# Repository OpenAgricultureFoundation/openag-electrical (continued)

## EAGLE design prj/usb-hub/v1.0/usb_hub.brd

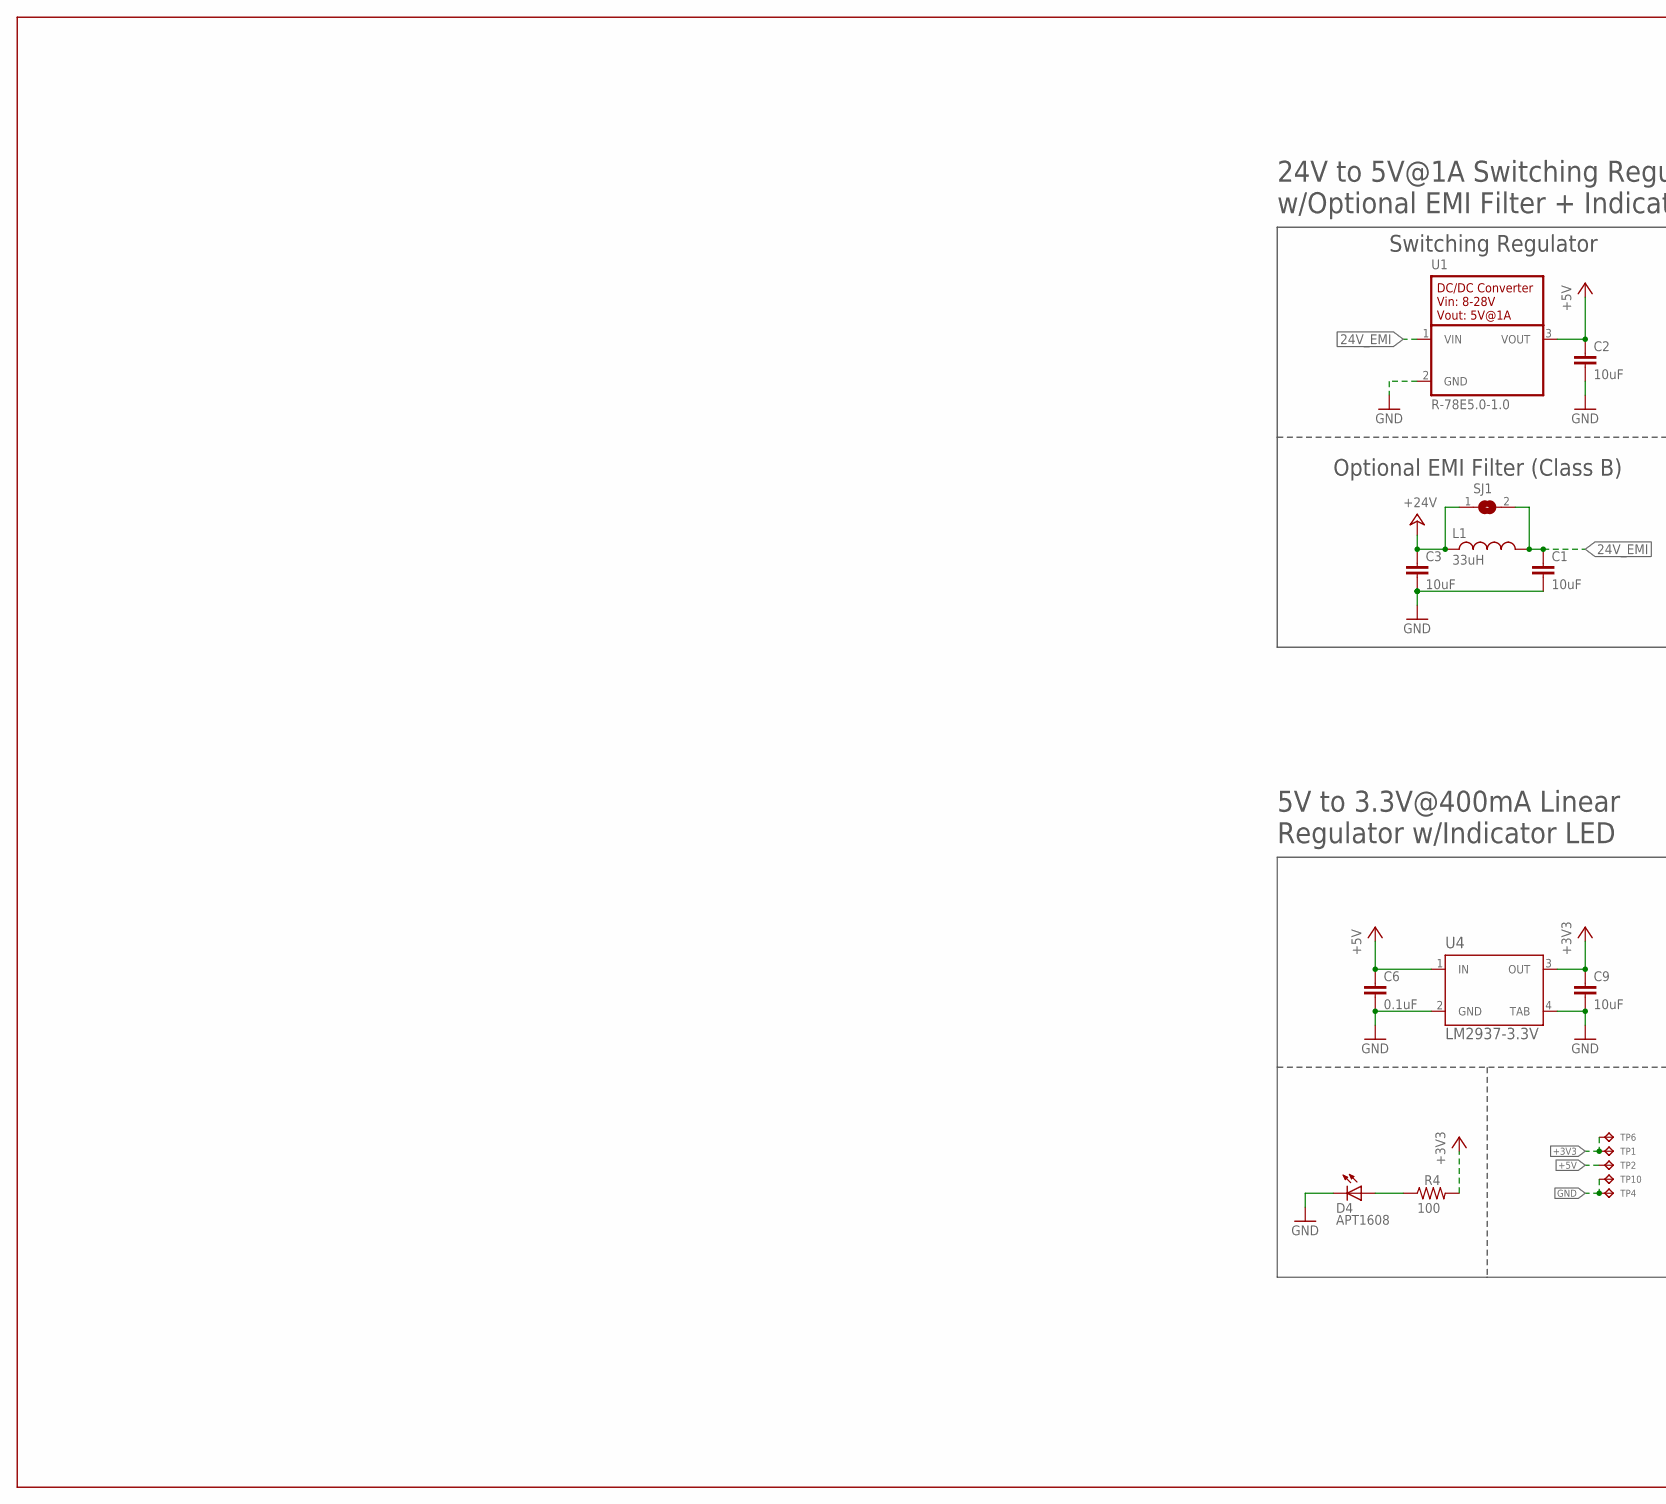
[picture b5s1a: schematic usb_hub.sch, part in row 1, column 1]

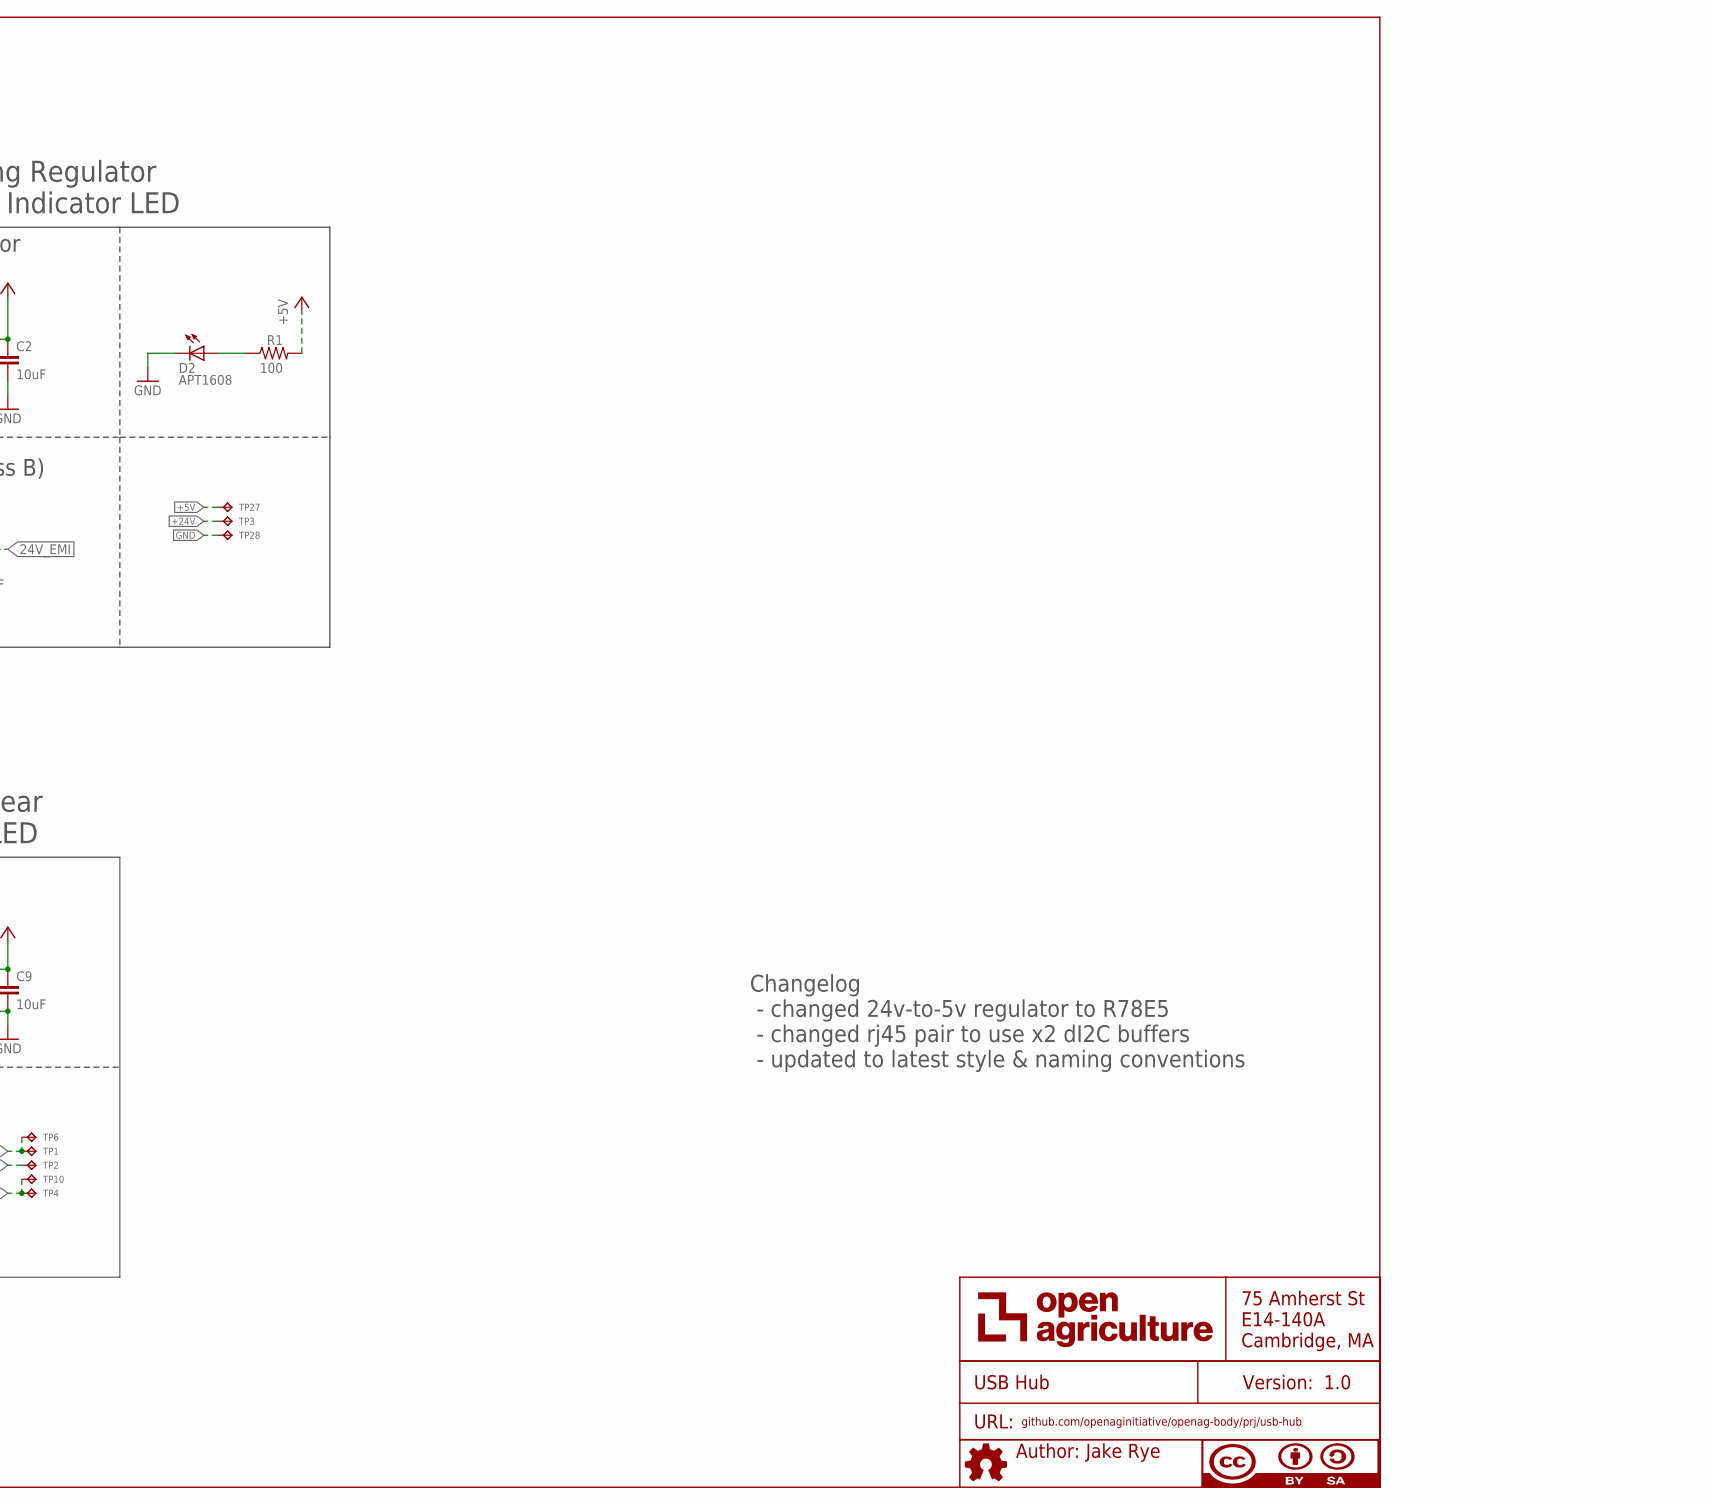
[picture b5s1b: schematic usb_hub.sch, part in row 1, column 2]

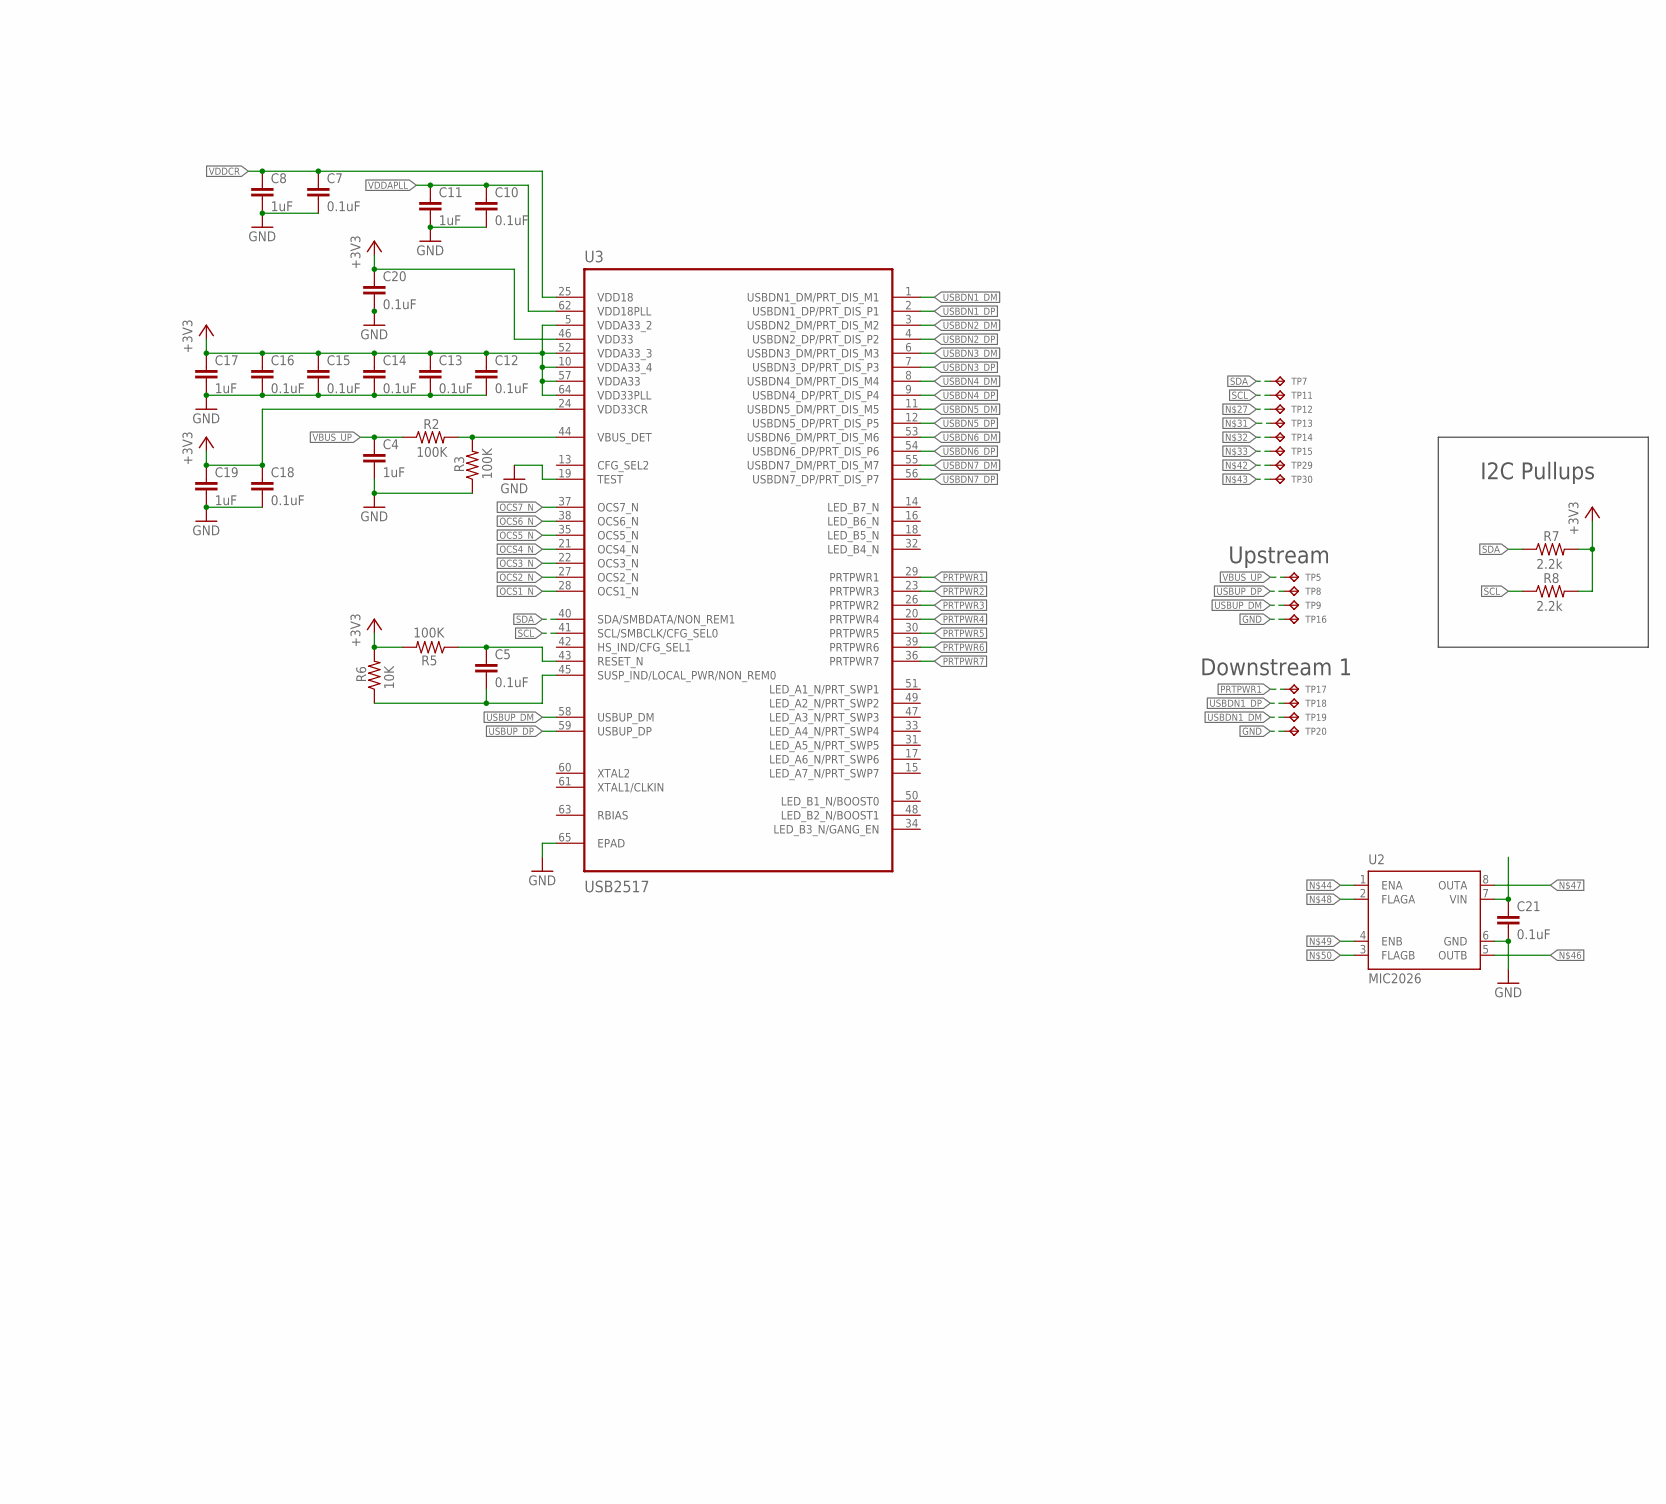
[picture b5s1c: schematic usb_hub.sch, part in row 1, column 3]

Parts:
C1, C2, C3, C9: 10uF; C0805
C4, C8, C11, C17, C19: 1uF; C0603
C5, C6, C7, C10, C12, C13, C14, C15, C16, C18, C20, C21: 0.1uF; C0603
D2, D4: APT1608; CHIPLED_0603
L1: 33uH; 29333C
R1, R4: 100; RC0603N
R2, R3, R5: 100K; RC0603N
R6: 10K; RC0603N
R7, R8: 2.2k; RC0603N
SJ1: SOLDERJUMPERREFLOW_NOPASTE; SJ1
TP1, TP2, TP4, TP5, TP6, TP7, TP8, TP9, TP10, TP11, TP12, TP13, TP14, TP15, TP16, TP17, TP18, TP19, TP20, TP29, TP30: TPTP04R; TP04R
TP3, TP27, TP28: TPTP06R; TP06R
U1: R-78E5.0-1.0
U2: MIC2026; SOIC8
U3: USB2517; QFN50P900X900X100-65N
U4: LM2937-3.3V; MP04A
U$6: AUTHOR
U$7: TITLE

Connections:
24V_EMI: C1.1, L1.2, SJ1.2, U1.1 (VIN)
+3V3: C9.1, C12.1, C13.1, C14.1, C15.1, C16.1, C17.1, C18.1, C19.1, C20.1, R4.2, R5.2, R6.2, R7.2, R8.2, TP1.1, TP6.1, U3.5 (VDDA33_2), U3.10 (VDDA33_4), U3.24 (VDD33CR), U3.46 (VDD33), U3.52 (VDDA33_3), U3.57 (VDDA33), U3.64 (VDD33PLL), U4.3 (OUT)
+5V: C2.1, C6.1, R1.2, TP2.1, TP27.TP, U1.3 (VOUT), U4.1 (IN)
+24V: C3.1, L1.1, SJ1.1, TP3.TP
GND: C1.2, C2.2, C3.2, C4.2, C6.2, C7.2, C8.2, C9.2, C10.2, C11.2, C12.2, C13.2, C14.2, C15.2, C16.2, C17.2, C18.2, C19.2, C20.2, C21.2, D2.C, D4.C, R3.1, TP4.1, TP10.1, TP16.1, TP20.1, TP28.TP, U1.2 (GND), U2.6 (GND), U3.19 (TEST), U3.65 (EPAD), U4.2 (GND), U4.4 (TAB)
unnamed: R2.2, R3.2, U3.44 (VBUS_DET)
unnamed: D4.A, R4.1
unnamed: D2.A, R1.1
unnamed: C5.1, R5.1, U3.43 (RESET_N)
unnamed: C21.1, U2.7 (VIN)
unnamed: C5.2, R6.1, U3.45 (SUSP_IND/LOCAL_PWR/NON_REM0)
OCS1_N: U3.28 (OCS1_N)
OCS2_N: U3.27 (OCS2_N)
OCS3_N: U3.22 (OCS3_N)
OCS4_N: U3.21 (OCS4_N)
OCS5_N: U3.35 (OCS5_N)
OCS6_N: U3.38 (OCS6_N)
OCS7_N: U3.37 (OCS7_N)
PRTPWR1: TP17.1, U3.29 (PRTPWR1)
PRTPWR2: U3.23 (PRTPWR3)
PRTPWR3: U3.26 (PRTPWR2)
PRTPWR4: U3.20 (PRTPWR4)
PRTPWR5: U3.30 (PRTPWR5)
PRTPWR6: U3.39 (PRTPWR6)
PRTPWR7: U3.36 (PRTPWR7)
SCL: R8.1, TP11.1, U3.41 (SCL/SMBCLK/CFG_SEL0)
SDA: R7.1, TP7.1, U3.40 (SDA/SMBDATA/NON_REM1)
USBDN1_DM: TP19.1, U3.1 (USBDN1_DM/PRT_DIS_M1)
USBDN1_DP: TP18.1, U3.2 (USBDN1_DP/PRT_DIS_P1)
USBDN2_DM: U3.3 (USBDN2_DM/PRT_DIS_M2)
USBDN2_DP: U3.4 (USBDN2_DP/PRT_DIS_P2)
USBDN3_DM: U3.6 (USBDN3_DM/PRT_DIS_M3)
USBDN3_DP: U3.7 (USBDN3_DP/PRT_DIS_P3)
USBDN4_DM: U3.8 (USBDN4_DM/PRT_DIS_M4)
USBDN4_DP: U3.9 (USBDN4_DP/PRT_DIS_P4)
USBDN5_DM: U3.11 (USBDN5_DM/PRT_DIS_M5)
USBDN5_DP: U3.12 (USBDN5_DP/PRT_DIS_P5)
USBDN6_DM: U3.53 (USBDN6_DM/PRT_DIS_M6)
USBDN6_DP: U3.54 (USBDN6_DP/PRT_DIS_P6)
USBDN7_DM: U3.55 (USBDN7_DM/PRT_DIS_M7)
USBDN7_DP: U3.56 (USBDN7_DP/PRT_DIS_P7)
USBUP_DM: TP9.1, U3.58 (USBUP_DM)
USBUP_DP: TP8.1, U3.59 (USBUP_DP)
VBUS_UP: C4.1, R2.1, TP5.1
VDDAPLL: C10.1, C11.1, U3.62 (VDD18PLL)
VDDCR: C7.1, C8.1, U3.25 (VDD18)

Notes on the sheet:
5V to 3.3V@400mA Linear Regulator w/Indicator LED
24V to 5V@1A Switching Regulator w/Optional EMI Filter + Indicator LED
Switching Regulator
Optional EMI Filter (Class B)
Changelog - changed 24v-to-5v regulator to R78E5 - changed rj45 pair to use x2 dI2C buffers - updated to latest style & naming conventions
Upstream
I2C Pullups
Downstream 1

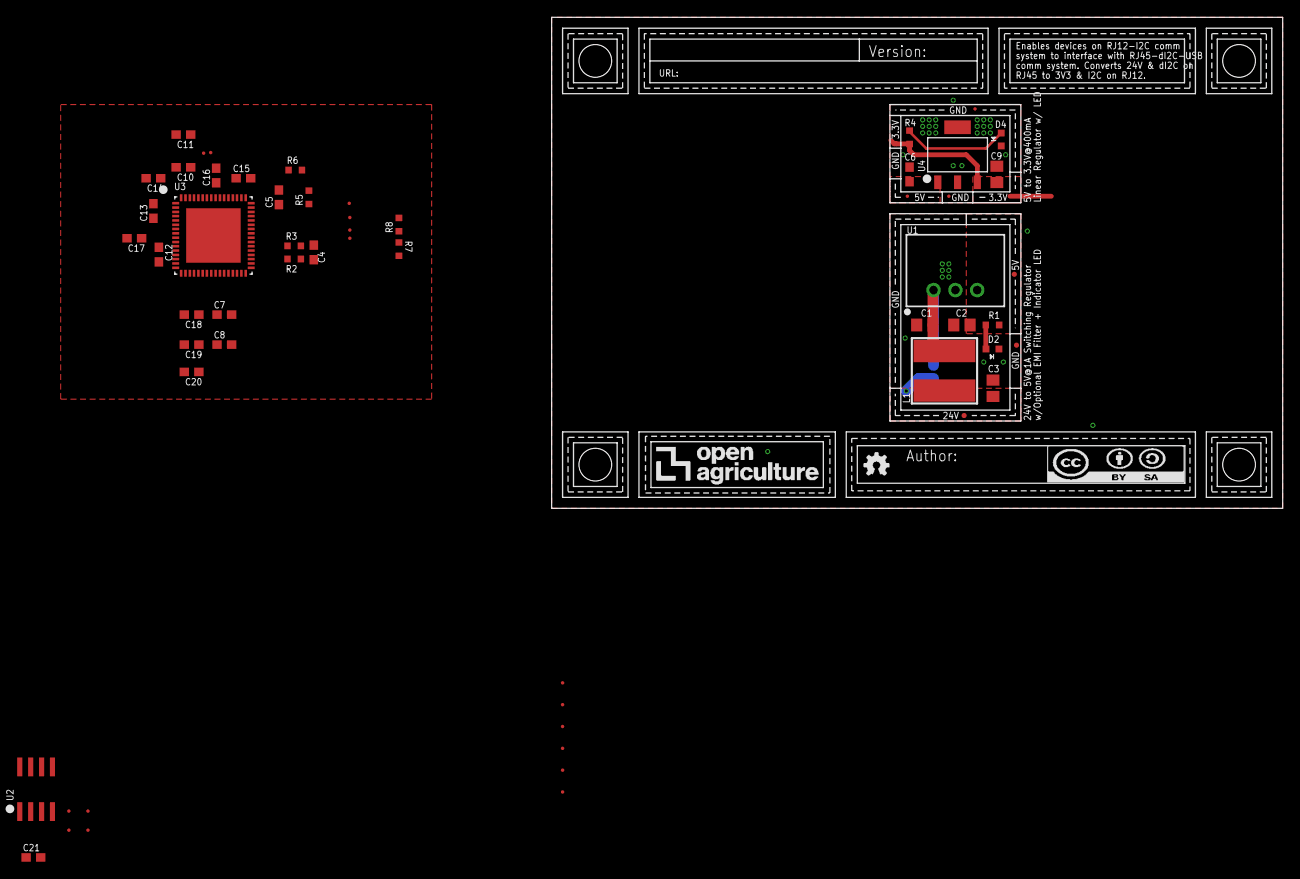
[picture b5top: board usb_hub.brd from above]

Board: 2 copper layers, 85.1 x 57.1 mm, 68 parts (1 on the bottom side), 21 nets.

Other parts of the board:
U$1, U$2, U$3, U$4: CORNER
U$5: LOGO
